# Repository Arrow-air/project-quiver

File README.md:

# Project Quiver

**An open-source, modular quadcopter platform for developers and operators.**

Project Quiver is a 25 kg MTOW drone with 5-8 kg payload capacity, three hot-swappable attachment interfaces, and a distributed electronics architecture. Built for reliability, field serviceability, and customization.

Developed by [Arrow Air](https://arrowair.com) and released under the CERN Open Hardware Licence.

## Key Features

- **Modular payload system** — Three quick-release interfaces (bottom, left, right) for mission equipment
- **Dual GNSS with RTK** — Centimeter-level positioning with backup redundancy
- **Distributed PCB architecture** — Four custom boards that can be individually serviced
- **25-31 min hover endurance** — Tattu 14S 30Ah smart battery with Hobbywing X6 Plus propulsion
- **ArduPilot firmware** — Standard QGroundControl/Mission Planner compatibility
- **Weatherproof design** — Sealed cockpit with rain canopies and drip-proof geometry

## Documentation

📖 **[Full Documentation](https://arrowair.com/quiver/)** — Platform overview, capabilities, and roadmap

The `docs/` folder is hosted on the [Arrow website](https://arrowair.com/quiver/).

| Resource | Description |
|----------|-------------|
| [Assembly Guides](https://arrowair.com/quiver/category/manufacturing/) | Step-by-step build instructions |
| [Engineering Reports](https://arrowair.com/quiver/category/reference--engineering-reports/) | Technical details for each prototype |
| [Meeting Notes](https://github.com/Arrow-air/project-quiver/wiki) | Engineering call notes |

## Repository Structure

```
project-quiver/
├── docs/                    # Documentation (hosted at arrowair.com/quiver)
├── src/
│   ├── quiver/              # CAD assembly — build123d Python package
│   ├── pcb/                 # KiCad PCB designs (4 custom boards)
│   ├── printing/            # 3D print profiles and settings
│   └── manufacturing/       # DXFs and cut sheets for CNC/laser
├── flight-test/             # Historical flight test logs
└── task-grant-bounty/       # Bounty and grant task specifications
```

### CAD Assembly

The CAD source is a [build123d](https://github.com/gumyr/build123d) Python package that composes STEP files into the full drone assembly. This enables programmatic CAD generation and version-controlled mechanical design. See [`src/quiver/`](src/quiver/) for details.

For online viewing, an interactive Fusion link of the complete Quiver assembly is available [here](https://a360.co/4kQC2ny).

For viewing online, 
## Getting Started

**Want to build one?** Start with the [Assembly Guides](https://arrowair.com/quiver/category/manufacturing/).

**Want to develop attachments?** Check out:
- [Possible Attachment List](task-grant-bounty/equipment/attachment/0001-possible_attachment_list/information-note.md)
- [Priority Attachment Requirements](task-grant-bounty/equipment/attachment/0002-detailed_attachment_requirement_for_bounty/information-note.md)

**Want a dev-kit?** Dev-kit drones are available for loan to developers with promising projects. Join the [Arrow Discord](https://discord.gg/arrow) to learn more.

## Contributing

We welcome contributions across:
- **Attachments** — Design new payloads for the modular interfaces
- **Electronics** — PCB improvements and new sensor integrations  
- **Mechanical** — Structural design and manufacturing optimization
- **Software** — ArduPilot configs, companion computer features, tooling
- **Documentation** — Guides, tutorials, and translations

See [CONTRIBUTING.md](CONTRIBUTING.md) for guidelines.

## Community

- **Discord** — [discord.gg/arrow](https://discord.gg/arrow)
- **DAO Forum** — [dao.arrowair.com](https://dao.arrowair.com)
- **Flight Tracking** — [project-flight-tracking.vercel.app](https://project-flight-tracking.vercel.app/)

## License

[CERN Open Hardware Licence Version 2 - Strongly Reciprocal (CERN-OHL-S)](LICENSE)

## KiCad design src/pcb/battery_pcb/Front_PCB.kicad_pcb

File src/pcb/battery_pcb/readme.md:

PCB files are up to date as of 01/05/26 (Front PCB V1.3, the board on the Dev-Kit aircraft). V1.2 gerbers remain in `production/` for reference.

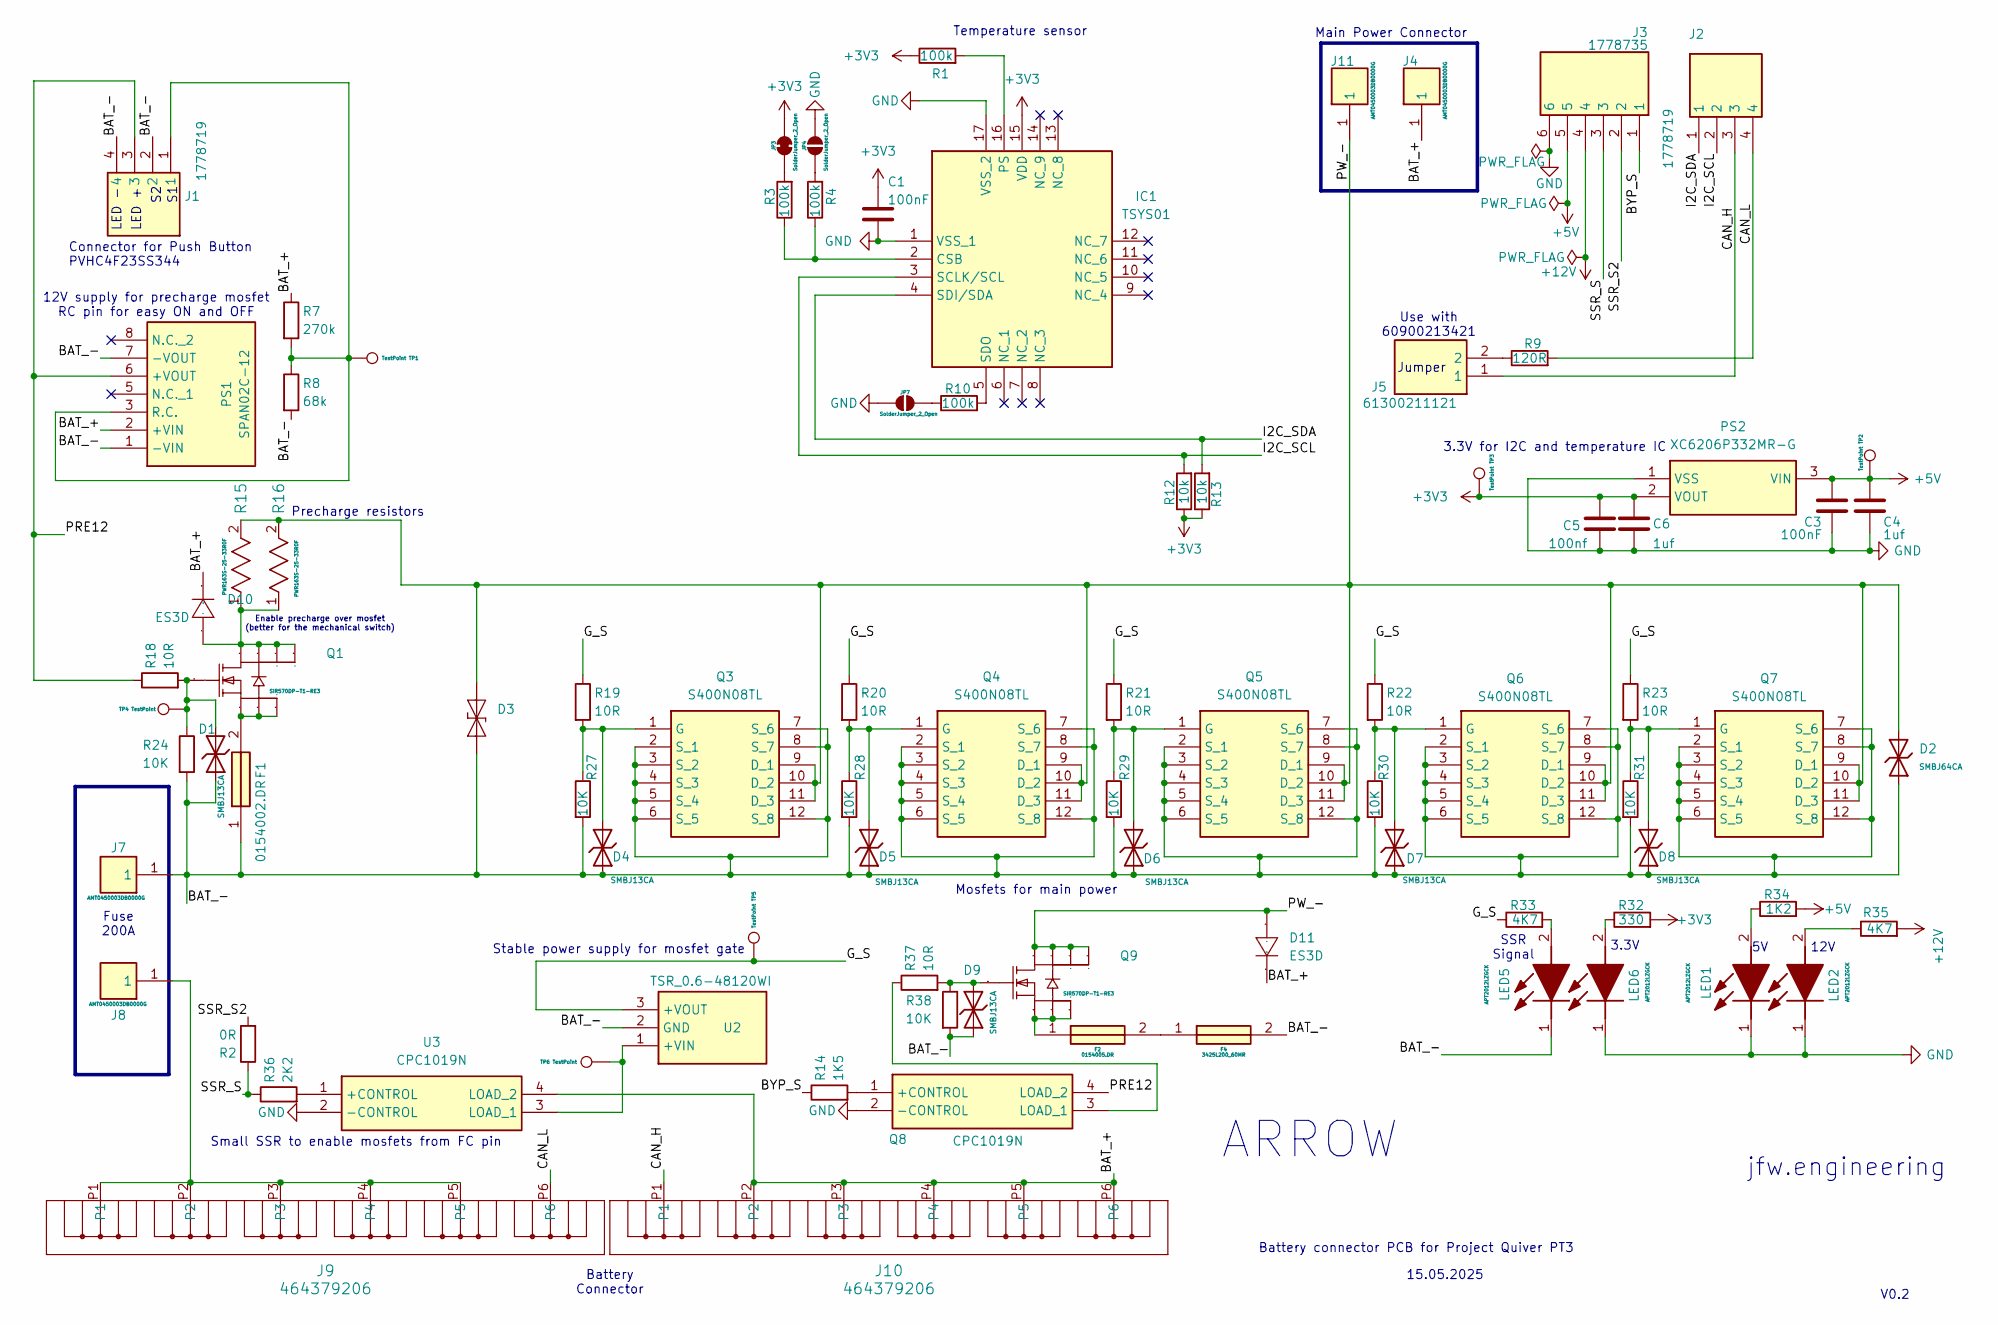
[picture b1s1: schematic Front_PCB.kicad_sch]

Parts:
C1, C3: 100nF; C_0805_2012Metric_Pad1.18x1.45mm_HandSolder
C4, C6: 1uf; C_0805_2012Metric_Pad1.18x1.45mm_HandSolder
C5: 100nf; C_0805_2012Metric_Pad1.18x1.45mm_HandSolder
D1, D4, D5, D6, D7, D8, D9: SMBJ13CA; D_SMB; Part SMBJ13CA; LCSC C19077568
D2: SMBJ64CA; D_SMB; Breakdown Voltage 78.6V; Part SMBJ64CA; LCSC C41376099
D3: SMC_L6.9-W5.9-LS7.9-BI; Manufacturer Part SMCJ75CA/TR13; LCSC Part Name SMCJ75CA/TR13
D10, D11: ES3D; D_SMC(DO-214AB); Manufacturer Part ES3D; LCSC Part Name ES3D
F1: 0154002.DR; 0154002DR; Mouser Part Number 576-0154002.DR
F2: 0154005.DR; 0154005DR; Mouser Part Number 576-0154005.DR
F4: 3425L200_60MR; FUSC8664X180N; Mouser Part Number 576-3425L200/60MR
IC1: TSYS01; QFN65P400X400X90-17N; Mouser Part Number 824-TSYS01
J1, J2: 1778719; Mouser Part Number 651-1778719
J3: 1778735; Mouser Part Number 651-1778735
J4, J7, J8, J11: AMT0450003DB0000G; Mouser Part Number 523-AMT0450003DB000G
J5: 61300211121; HDRV2W110P0X254_1X2_508X254X854P; Mouser Part Number 710-61300211121
J9, J10: 464379206; CONN_SD-46437-9000_06_MOL
JP3: SolderJumper_2_Open; SolderJumper-2_P1.3mm_Bridged2Bar_RoundedPad1.0x1.5mm
JP4, JP7: SolderJumper_2_Open; SolderJumper-2_P1.3mm_Open_RoundedPad1.0x1.5mm
LED1, LED2, LED5, LED6: APT2012LZGCK; LEDC2012X85N; Mouser Part Number 604-APT2012LZGCK
PS1: SPAN02C-12; SPAN02C12; Mouser Part Number 709-SPAN02C-12
PS2: XC6206P332MR-G; SOT95P280X130-3N; Mouser Part Number 865-XC6206P332MR-G
Q1, Q9: SIR570DP-T1-RE3; POWERPAK-SO-8_L5.9-W4.9-P1.27-LS6.2-BL; Mouser Part Number 781-SIR804DP-T1-GE3
Q3, Q4, Q5, Q6, Q7: S400N08TL; IAUT150N10S5N035ATMA1; Mouser Part Number 726-IPT017N12NM6ATMA
Q8: CPC1019N; SOP254P610X218-4N; Mouser Part Number 849-CPC1019N
R1, R3, R4, R10: 100k; R_0805_2012Metric_Pad1.20x1.40mm_HandSolder
R2: 0R; R_0805_2012Metric_Pad1.20x1.40mm_HandSolder
R7: 270k; R_0805_2012Metric_Pad1.20x1.40mm_HandSolder
R8: 68k; R_0805_2012Metric_Pad1.20x1.40mm_HandSolder
R9: 120R; R_0805_2012Metric_Pad1.20x1.40mm_HandSolder
R12, R13: 10k; R_0805_2012Metric_Pad1.20x1.40mm_HandSolder
R14: 1K5; R_0805_2012Metric_Pad1.20x1.40mm_HandSolder
R15, R16: PWR163S-25-33R0F; RES_PWR163_BRN; PARTREV 0716
R18, R19, R20, R21, R22, R23, R37: 10R; R_0805_2012Metric_Pad1.20x1.40mm_HandSolder
R24, R27, R28, R29, R30, R31, R38: 10K; R_0805_2012Metric_Pad1.20x1.40mm_HandSolder
R32: 330; R_0805_2012Metric_Pad1.20x1.40mm_HandSolder
R33, R35: 4K7; R_0805_2012Metric_Pad1.20x1.40mm_HandSolder
R34: 1K2; R_0805_2012Metric_Pad1.20x1.40mm_HandSolder
R36: 2K2; R_0805_2012Metric_Pad1.20x1.40mm_HandSolder
TP1, TP2, TP3, TP4, TP5, TP6: TestPoint; TestPoint_Pad_D1.5mm
U2: TSR_0.6-48120WI; TSR0648120WI; Mouser Part Number 495-TSR0.6-48120WI
U3: CPC1019N; SOP254P610X218-4N; Mouser Part Number 849-CPC1019N

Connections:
+3V3: C1.1, C5.1, C6.1, IC1.15 (VDD), JP3.2 (B), PS2.2 (VOUT), R1.1, R12.1, R13.1, R32.2, TP3.1
+5V: C3.1, C4.1, J3.5, PS2.3 (VIN), R34.2, TP2.1
+12V: J3.4, R35.2
/BAT_+: D10.1, D11.1, J4.1, J10.P2, J10.P3, J10.P4, J10.P5, J10.P6, PS1.2 (+VIN), R7.1, U3.4 (LOAD_2)
/BAT_-: D1.1, D2.1, D3.1 (K), D4.1, D5.1, D6.1, D7.1, D8.1, D9.1, F1.1, F4.2, J1.2, J1.4, J7.1, LED5.1 (K), PS1.1 (-VIN), PS1.7 (-VOUT), Q3.2 (S_1), Q3.3 (S_2), Q3.4 (S_3), Q3.5 (S_4), Q3.6 (S_5), Q3.7 (S_6), Q3.8 (S_7), Q3.12 (S_8), Q4.2 (S_1), Q4.3 (S_2), Q4.4 (S_3), Q4.5 (S_4), Q4.6 (S_5), Q4.7 (S_6), Q4.8 (S_7), Q4.12 (S_8), Q5.2 (S_1), Q5.3 (S_2), Q5.4 (S_3), Q5.5 (S_4), Q5.6 (S_5), Q5.7 (S_6), Q5.8 (S_7), Q5.12 (S_8), Q6.2 (S_1), Q6.3 (S_2), Q6.4 (S_3), Q6.5 (S_4), Q6.6 (S_5), Q6.7 (S_6), Q6.8 (S_7), Q6.12 (S_8), Q7.2 (S_1), Q7.3 (S_2), Q7.4 (S_3), Q7.5 (S_4), Q7.6 (S_5), Q7.7 (S_6), Q7.8 (S_7), Q7.12 (S_8), R8.2, R24.2, R27.2, R28.2, R29.2, R30.2, R31.2, R38.2, U2.2 (GND)
/BYP_S: J3.1, R14.1
/CAN_H: J2.3, J5.1, J10.P1
/CAN_L: J2.4, J9.P6, R9.2
/G_S: R19.1, R20.1, R21.1, R22.1, R23.1, R33.1, TP5.1, U2.3 (+VOUT)
/I2C_SCL: IC1.3 (SCLK/SCL), J2.2, R12.2
/I2C_SDA: IC1.4 (SDI/SDA), J2.1, R13.2
/PRE12: J1.3, PS1.6 (+VOUT), Q8.4 (LOAD_2), R18.1
/PW_-: D2.2, D3.2 (A), D11.2, J11.1, Q3.9 (D_1), Q3.10 (D_2), Q3.11 (D_3), Q4.9 (D_1), Q4.10 (D_2), Q4.11 (D_3), Q5.9 (D_1), Q5.10 (D_2), Q5.11 (D_3), Q6.9 (D_1), Q6.10 (D_2), Q6.11 (D_3), Q7.9 (D_1), Q7.10 (D_2), Q7.11 (D_3), Q9.5 (D), Q9.6 (D), Q9.7 (D), Q9.8 (D), R15.2, R16.2
/SSR_S: J3.3, R2.1, R36.1
/SSR_S2: J3.2, R2.2
GND: C1.2, C3.2, C4.2, C5.2, C6.2, IC1.1 (VSS_1), IC1.17 (VSS_2), J3.6, JP4.2 (B), JP7.1 (A), LED1.1 (K), LED2.1 (K), LED6.1 (K), PS2.1 (VSS), Q8.2 (-CONTROL), U3.2 (-CONTROL)
unnamed: D10.2, Q1.5 (D), Q1.6 (D), Q1.7 (D), Q1.8 (D), R15.1, R16.1
unnamed: F1.2, Q1.1 (S), Q1.2 (S), Q1.3 (S)
unnamed: F2.1, Q9.1 (S), Q9.2 (S), Q9.3 (S)
unnamed: F2.2, F4.1
unnamed: IC1.2 (CSB), R3.1, R4.1
unnamed: IC1.16 (PS), R1.2
unnamed: IC1.5 (SDO), R10.2
unnamed: J5.2, R9.1
unnamed: J8.1, J9.P1, J9.P2, J9.P3, J9.P4, J9.P5
unnamed: JP3.1 (A), R3.2
unnamed: JP4.1 (A), R4.2
unnamed: JP7.2 (B), R10.1
unnamed: LED1.2 (A), R34.1
unnamed: LED2.2 (A), R35.1
unnamed: LED5.2 (A), R33.2
unnamed: LED6.2 (A), R32.1
unnamed: J1.1, PS1.3 (R.C.), R7.2, R8.1, TP1.1
unnamed: D1.2, Q1.4 (G), R18.2, R24.1, TP4.1
unnamed: D4.2, Q3.1 (G), R19.2, R27.1
unnamed: D5.2, Q4.1 (G), R20.2, R28.1
unnamed: D6.2, Q5.1 (G), R21.2, R29.1
unnamed: D7.2, Q6.1 (G), R22.2, R30.1
unnamed: D8.2, Q7.1 (G), R23.2, R31.1
unnamed: Q8.1 (+CONTROL), R14.2
unnamed: Q8.3 (LOAD_1), R37.1
unnamed: D9.2, Q9.4 (G), R37.2, R38.1
unnamed: TP6.1, U2.1 (+VIN), U3.3 (LOAD_1)
unnamed: R36.2, U3.1 (+CONTROL)

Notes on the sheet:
15.05.2025
Connector for Push Button PVHC4F23SS344
Battery connector PCB for Project Quiver PT3
SSR Signal
3.3V
12V supply for precharge mosfet RC pin for easy ON and OFF
Use with 60900213421
12V
Battery Connector
ARROW
Temperature sensor
Small SSR to enable mosfets from FC pin
3.3V for I2C and temperature IC
Jumper
Mosfets for main power
LED -
Stable power supply for mosfet gate
V0.2
jfw.engineering
Enable precharge over mosfet (better for the mechanical switch)
LED +
Main Power Connector
Fuse 200A
Precharge resistors

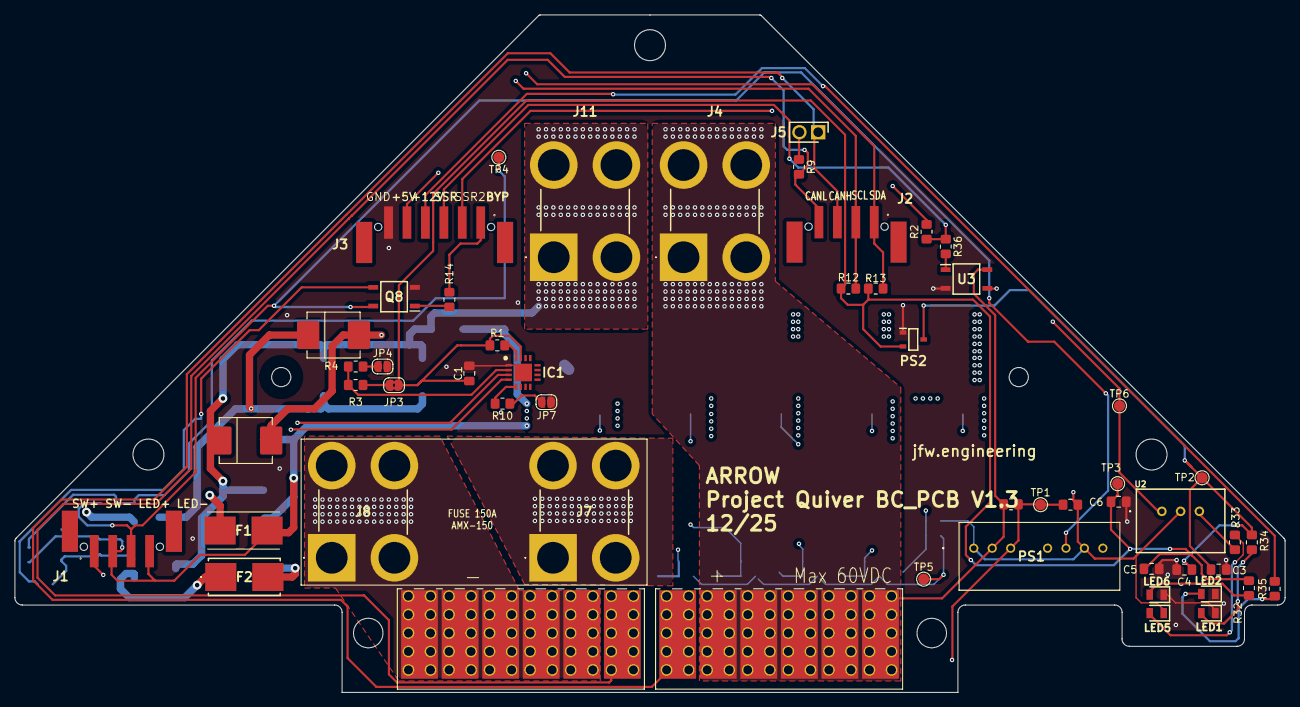
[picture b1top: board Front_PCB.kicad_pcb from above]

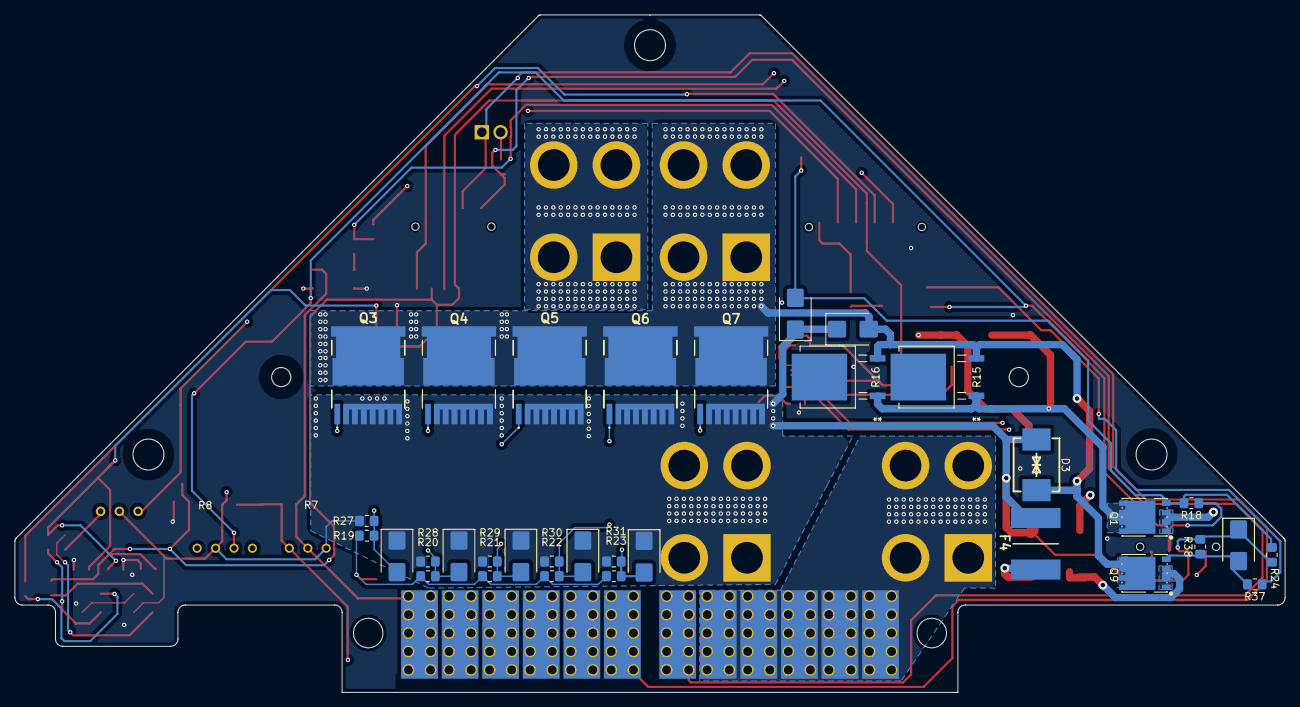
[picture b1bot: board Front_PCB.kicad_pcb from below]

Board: 4 copper layers, 172.2 x 91.8 mm, 87 parts (33 on the bottom side), 44 nets.

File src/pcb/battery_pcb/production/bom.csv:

Designator,Footprint,Quantity,Value,LCSC Part #
"C1, C3, C5",0805,3,100nF,
"C4, C6",0805,2,1uf,
"D1, D4, D5, D6, D7, D8, D9",D_SMB,7,SMBJ13CA,C19077568
"D10, D11",D_SMC(DO-214AB),2,ES3D,
D2,D_SMB,1,SMBJ64CA,C41376099
D3,SMC_L6.9-W5.9-LS7.9-BI,1,~,
F1,0154002DR,1,0154002.DR,
F2,0154005DR,1,0154005.DR,
F4,FUSC8664X180N,1,3425L200_60MR,
IC1,QFN65P400X400X90-17N,1,TSYS01,
"J1, J2",1778719,2,1778719,
"J10, J9",CONN_SD-46437-9000_06_MOL,2,464379206,
"J11, J4, J7, J8",AMT0450003DB0000G,4,AMT0450003DB0000G,
J3,1778735,1,1778735,
J5,HDRV2W110P0X254_1X2_508X254X854P,1,61300211121,
"LED1, LED2, LED5, LED6",LEDC2012X85N,4,APT2012LZGCK,
PS1,SPAN02C12,1,SPAN02C-12,
PS2,SOT95P280X130-3N,1,XC6206P332MR-G,
"Q1, Q9",POWERPAK-SO-8_L5.9-W4.9-P1.27-LS6.2-BL,2,SIR570DP-T1-RE3,
"Q3, Q4, Q5, Q6, Q7",IAUT150N10S5N035ATMA1,5,S400N08TL,
"Q8, U3",SOP254P610X218-4N,2,CPC1019N,
"R1, R10, R3, R4",0805,4,100k,
"R12, R13, R24, R27, R28, R29, R30, R31, R38",0805,9,10k,
R14,0805,1,1K5,
"R15, R16",RES_PWR163_BRN,2,PWR163S-25-33R0F,
"R18, R19, R20, R21, R22, R23, R37",0805,7,10R,
R2,0805,1,0R,
R32,0805,1,330,
"R33, R35",0805,2,4K7,
R34,0805,1,1K2,
R36,0805,1,2K2,
R7,0805,1,270k,
R8,0805,1,68k,
R9,0805,1,120R,
"TP1, TP2, TP3, TP4, TP5, TP6",TestPoint_Pad_D1.5mm,6,TestPoint,
U2,TSR0648120WI,1,TSR_0.6-48120WI,

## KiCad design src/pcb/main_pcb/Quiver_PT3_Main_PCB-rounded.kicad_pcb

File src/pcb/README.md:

# PCB Designs

KiCad projects for the Quiver's distributed PCB architecture.

## Board projects

| Directory | BOM | KiCad project | Description |
|---|---|---|---|
| `battery_pcb/` | 3320 | `Front_PCB` (V1.3) | Battery PCB — power switching and protection |
| `main_pcb/` | 3310 | `Quiver_PT3_Main_PCB-rounded` (V1.2) | Main PCB — power and data distribution hub. V1.2 is the board on the Dev-Kit aircraft. |
| `fc_pcb/` | 3330 | `Quiver_PT3_FC_PCB` | Flight Controller PCB — Pix32 V6 adapter board |
| `attach_pcb/` | 3331 | `QuiverAttachPCB` (V1.4) | Attachment Interface PCB (x3) |

Production gerbers live in each project's `production/` folder. Design
history, update notes, and superseded board revisions remain with the
bounty tasks under
[`task-grant-bounty/pt3/electronics/`](../../task-grant-bounty/pt3/electronics/).

## STEP export workflow

Each KiCad project can export a 3D STEP model of the assembled board
(`kicad-cli pcb export step --subst-models <board>.kicad_pcb`). The CAD
assembly uses these models:

```
pcb/<board>/  ──(KiCad 3D export)──►  ../quiver/equipment/pcb/steps/vendor/{BOM}_{name}.step
```

For example, `main_pcb` is `3310_main_pcb.step` and `battery_pcb` is
`3320_bc_pcb.step` in `../quiver/equipment/pcb/steps/vendor/`.

The CAD models also carry parts whose 3D models are not in these KiCad
libraries: `3320_bc_pcb.step` includes the 3324 heatsink with its screws
and a few connector and component bodies. A plain KiCad export is missing
them, so before replacing a CAD model, check that its board body matches
the KiCad source and carry those parts over. The board bodies in 3310 and
3320 match the V1.2 and V1.3 sources exactly.

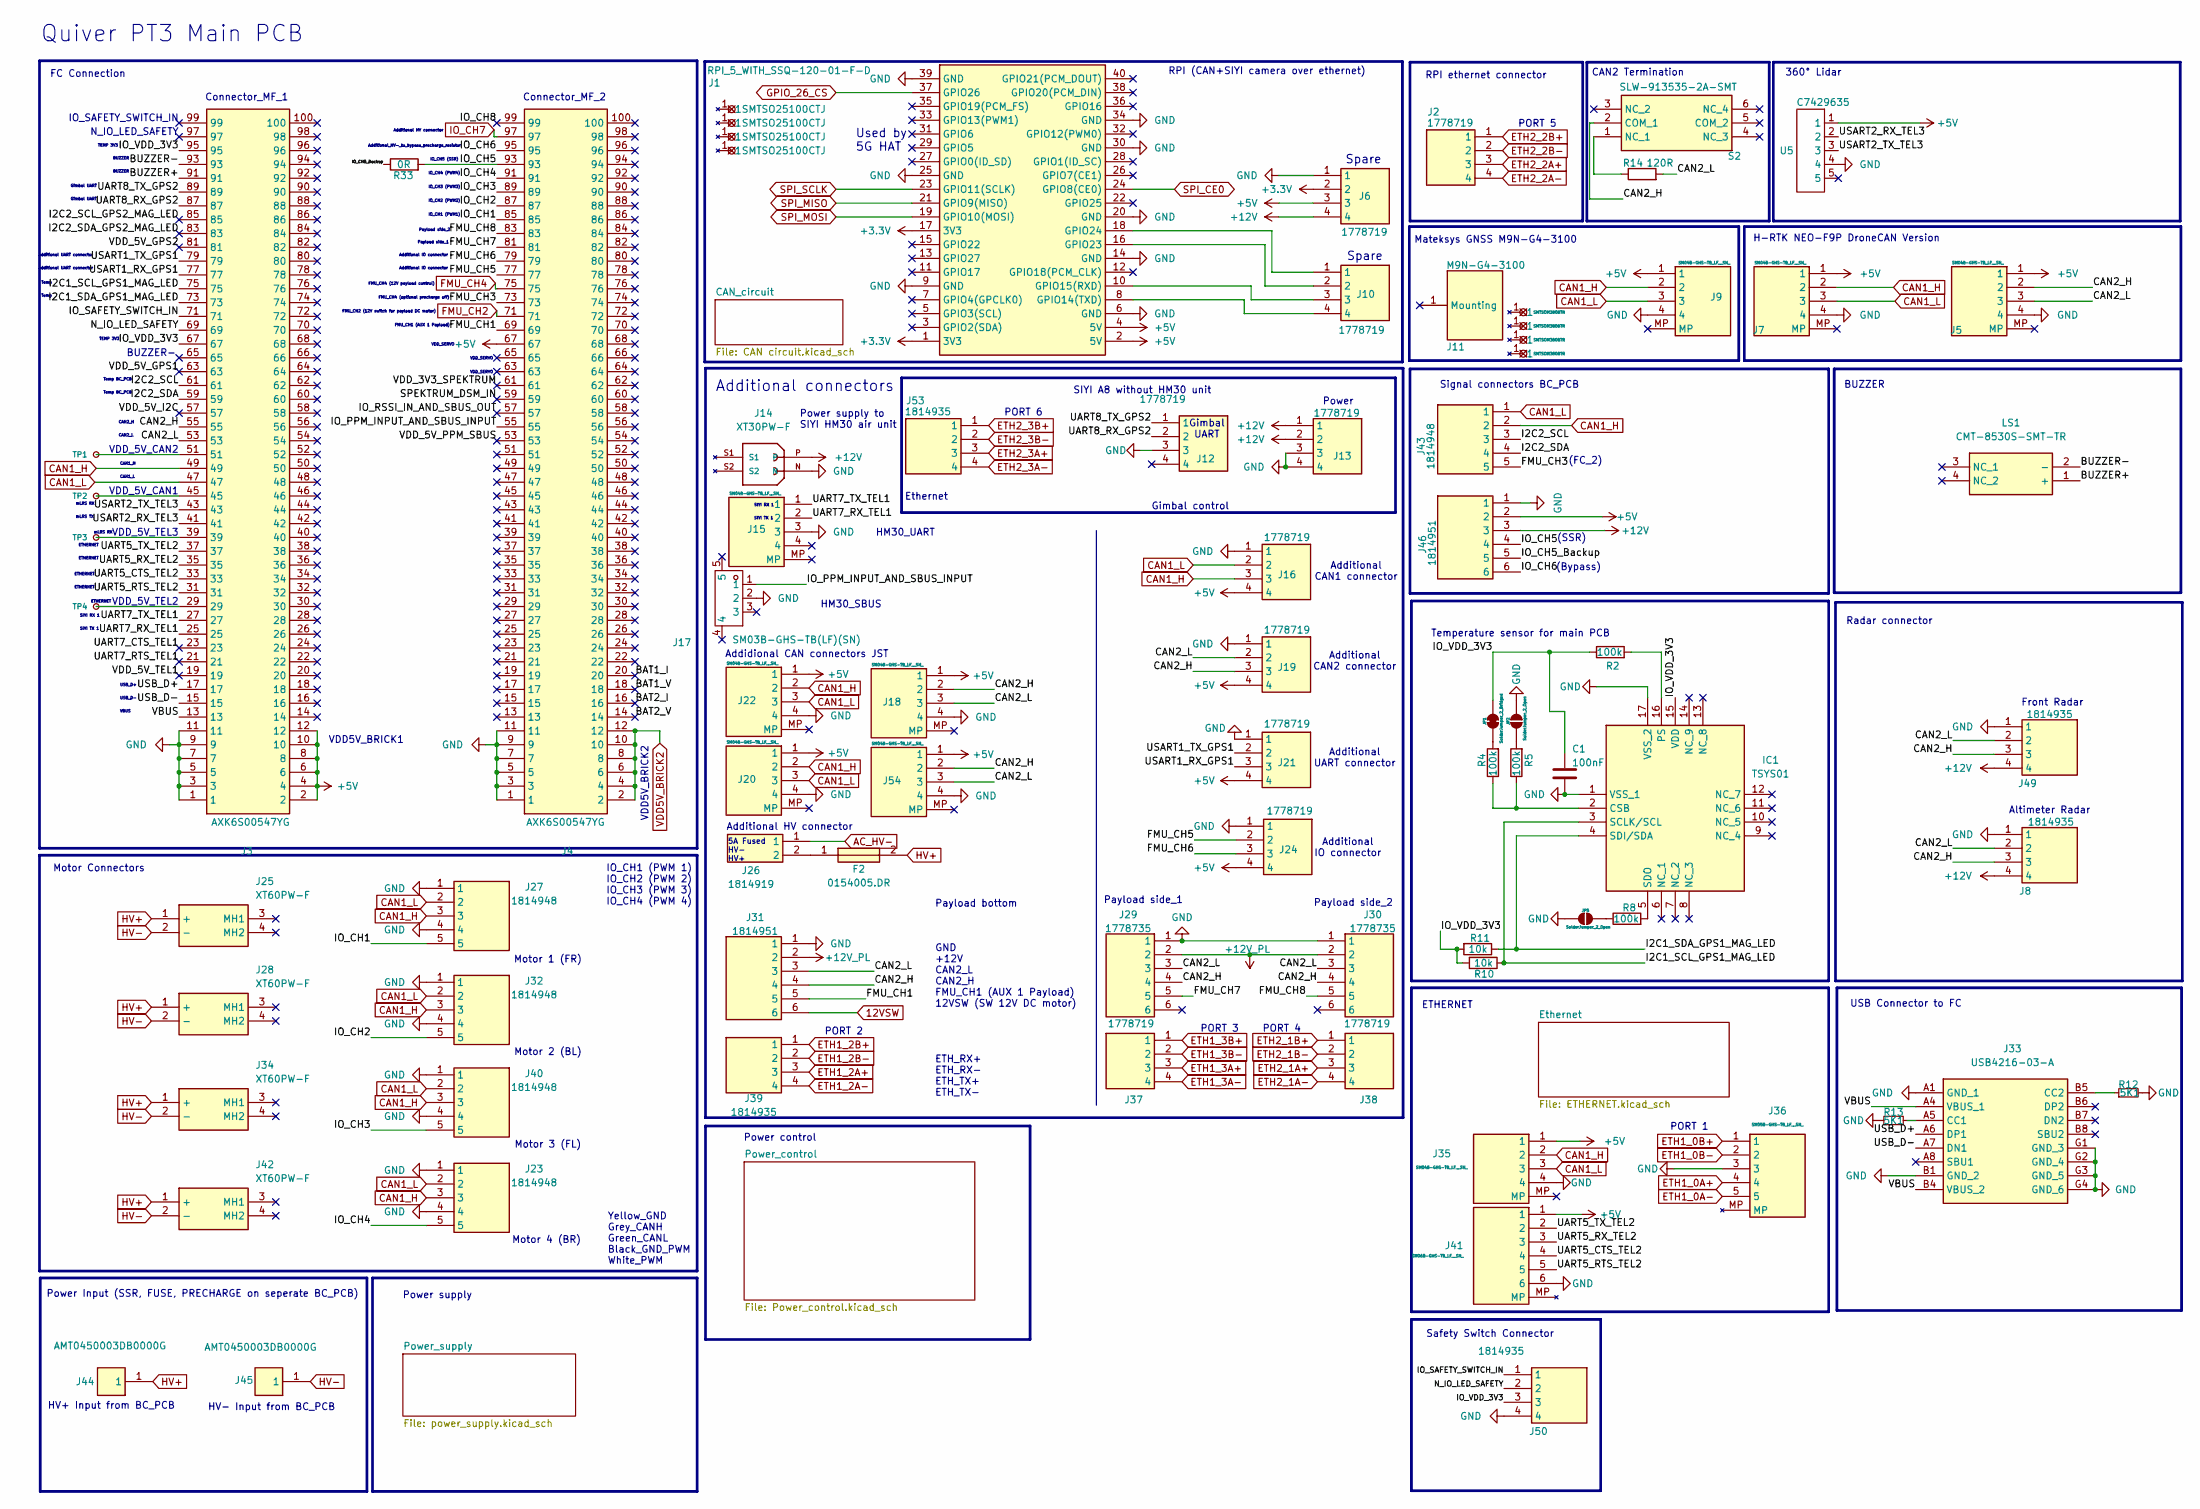
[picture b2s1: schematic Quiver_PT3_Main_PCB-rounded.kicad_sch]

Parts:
C1: 100nF; C_0805_2012Metric_Pad1.18x1.45mm_HandSolder; MPN CC0805KRX7R9BB104
F2: 0154005.DR; 0154005DR; Mouser Part Number 576-0154005.DR
IC1: TSYS01; QFN65P400X400X90-17N; Mouser Part Number 824-TSYS01
J1: RPI_5_WITH_SSQ-120-01-F-D; SSM-120-XXX-DV; Mouser Part Number 200-SSQ12001FD
J2, J6, J10, J12, J13, J16, J19, J21, J24, J37, J38: 1778719; Mouser Part Number 651-1778719
J3, J4: AXK6S00547YG; MANUFACTURER_PART_NUMBER AXK5S00347YG; Mouser Part Number 769-AXK6S00547YG
J5, J7, J9, J15, J18, J20, J22, J35, J54: SM04B-GHS-TB_LF__SN_; SM04B-GHS-TB; Mouser Part Number N/A
J8, J39, J49, J50, J53: 1814935; Mouser Part Number 651-1814935
J11: M9N-G4-3100; Manufacturer_Part_Number SSQ-104-01-L-D
J14: XT30PW-F; XT30PW-F_AMASS_XT30PW-F; PARTREV 1.2
J17: SM03B-GHS-TB(LF)(SN); CONN-TH_SM03B-GHS-TB-LF-SN; Mouser Part Number 651-1814922
J23, J27, J32, J40, J43: 1814948; Mouser Part Number 651-1814948
J25, J28, J34, J42: XT60PW-F; XT60PWF; Manufacturer_Part_Number XT60PW-F
J26: 1814919; Mouser Part Number 651-1814919
J29, J30: 1778735; Mouser Part Number 651-1778735
J31, J46: 1814951; Mouser Part Number 651-1814951
J33: USB4216-03-A; USB421603A; Mouser Part Number 640-USB4216-03-A
J36: SM05B-GHS-TB_LF__SN_; SM05B-GHS-TB; Mouser Part Number N/A
J41: SM06B-GHS-TB_LF__SN_; SM06B-GHS-TB; Mouser Part Number N/A
J44, J45: AMT0450003DB0000G; Mouser Part Number 523-AMT0450003DB000G
JP1: SolderJumper_2_Bridged; SolderJumper-2_P1.3mm_Bridged2Bar_RoundedPad1.0x1.5mm
JP2, JP5: SolderJumper_2_Open; SolderJumper-2_P1.3mm_Open_RoundedPad1.0x1.5mm
LS1: CMT-8530S-SMT-TR; CMT8530SSMTTR; Mouser Part Number 490-CMT-8530S-SMT-TR
R2, R4, R5: 100k; R_0805_2012Metric_Pad1.20x1.40mm_HandSolder
R8: 100k; R_0805_2012Metric_Pad1.20x1.40mm_HandSolder; MPN RC0805FR-0710KL
R10, R11: 10k; R_0805_2012Metric_Pad1.20x1.40mm_HandSolder; MPN RC0805FR-0710KL
R12, R13: 5K1; R_0805_2012Metric_Pad1.20x1.40mm_HandSolder
R14: 120R; R_0805_2012Metric_Pad1.20x1.40mm_HandSolder; MPN RC0805FR-07120RL
R33: 0R; R_0805_2012Metric_Pad1.20x1.40mm_HandSolder
S2: SLW-913535-2A-SMT; SLW9135352ASMT; MPN SLW-913535-2A-SMT; Mouser Part Number 179-SLW-913535-2ASMT
TP1, TP2, TP3, TP4: TestPoint_Small; TestPoint_Pad_1.0x1.0mm
U3, U6, U7, U8: SMTSOM380BTR; SMD_BD6.0-D4.2; Manufacturer Part SMTSOM380BTR; LCSC Part Name YIYUAN(怡远) 电路板表贴圆螺母柱 PCB贴片连接器 M3x5.56xL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
U5: C7429635; CONN-TH_5P-P2.50_ZX-XH2.54-5PZZ; Mouser Part Number 651-1814935
U9, U10, U11, U12: SMTSO25100CTJ; SMD_BD5.6-L5.6-W5.6-D4.1; Manufacturer Part SMTSO25100CTJ; LCSC Part Name 雄和远景，电路板表贴圆螺母柱，M2.5X10，铜镀锡,1个

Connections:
12VSW: J31.6; also elsewhere on the board
+3.3V: J1.1 (3V3), J1.17 (3V3), J6.2; also elsewhere on the board
+5V: J1.2 (5V), J1.4 (5V), J3.2, J3.4, J3.6, J3.8, J3.10, J3.12, J4.67, J5.1, J6.3, J7.1, J9.1, J16.4, J18.1, J19.4, J20.1, J21.4, J22.1, J24.4, J35.1, J41.1, J46.2, J54.1, U5.1; also elsewhere on the board
+12V: J6.4, J8.4, J13.1, J13.2, J14.P, J46.3, J49.4; also elsewhere on the board
+12V_PL: J29.2, J30.2, J31.2; also elsewhere on the board
/ I2C2_SDA_GPS2_MAG_LED: J3.83
/BAT1_I: J4.20
/BAT1_V: J4.18
/BAT2_I: J4.16
/BAT2_V: J4.14
/BUZZER+: J3.91, LS1.1 (+)
/BUZZER-: J3.93, LS1.2 (-)
/CAN2_H: J3.55, J5.2, J8.3, J18.2, J19.3, J29.4, J30.4, J31.4, J49.3, J54.2, S2.2 (COM_1)
/CAN2_L: J3.53, J5.3, J8.2, J18.3, J19.2, J29.3, J30.3, J31.3, J49.2, J54.3, R14.2
/FMU_CH1: J4.69, J31.5
/FMU_CH3: J4.73, J43.5
/FMU_CH5: J4.77, J24.2
/FMU_CH6: J4.79, J24.3
/FMU_CH7: J4.81, J29.5
/FMU_CH8: J4.83, J30.5
/I2C1_SCL_GPS1_MAG_LED: IC1.3 (SCLK/SCL), J3.75, R10.1
/I2C1_SDA_GPS1_MAG_LED: IC1.4 (SDI/SDA), J3.73, R11.1
/I2C2_SCL: J3.61, J43.3
/I2C2_SCL_GPS2_MAG_LED: J3.85
/I2C2_SDA: J3.59, J43.4
/IO_CH1: J4.85, J27.5
/IO_CH2: J4.87, J32.5
/IO_CH3: J4.89, J40.5
/IO_CH4: J4.91, J23.5
/IO_CH5: J4.93, J46.4, R33.2
/IO_CH5_Backup: J46.5, R33.1
/IO_CH6: J4.95, J46.6
/IO_CH8: J4.99
/IO_PPM_INPUT_AND_SBUS_INPUT: J4.55, J17.1
/IO_RSSI_IN_AND_SBUS_OUT: J4.57
/IO_SAFETY_SWITCH_IN: J3.71, J50.1
/IO_VDD_3V3: C1.1, IC1.15 (VDD), J3.67, J3.95, J50.3, JP1.2 (B), R2.1, R10.2, R11.2
/N_IO_LED_SAFETY: J3.69, J50.2
/SPEKTRUM_DSM_IN: J4.59
/UART5_CTS_TEL2: J3.33, J41.4
/UART5_RTS_TEL2: J3.31, J41.5
/UART5_RX_TEL2: J3.35, J41.3
/UART5_TX_TEL2: J3.37, J41.2
/UART7_CTS_TEL1: J3.23
/UART7_RTS_TEL1: J3.21
/UART7_RX_TEL1: J3.25, J15.2
/UART7_TX_TEL1: J3.27, J15.1
/UART8_RX_GPS2: J3.87, J12.2
/UART8_TX_GPS2: J3.89, J12.1
/USART1_RX_GPS1: J3.77, J21.3
/USART1_TX_GPS1: J3.79, J21.2
/USART2_RX_TEL3: J3.41, U5.2
/USART2_TX_TEL3: J3.43, U5.3
/USB_D+: J3.17, J33.A6 (DP1)
/USB_D-: J3.15, J33.A7 (DN1)
/VBUS: J3.13, J33.A4 (VBUS_1), J33.B4 (VBUS_2)
/VDD_3V3_SPEKTRUM: J4.61
/VDD_5V_GPS1: J3.63
/VDD_5V_GPS2: J3.81
/VDD_5V_I2C: J3.57
/VDD_5V_PPM_SBUS: J4.53
/VDD_5V_TEL1: J3.19
AC_HV-: J26.1; also elsewhere on the board
CAN1_H: J3.49, J7.2, J9.2, J16.3, J20.2, J22.2, J23.3, J27.3, J32.3, J35.2, J40.3, J43.2; also elsewhere on the board
CAN1_L: J3.47, J7.3, J9.3, J16.2, J20.3, J22.3, J23.2, J27.2, J32.2, J35.3, J40.2, J43.1; also elsewhere on the board
ETH1_0A+: J36.4; also elsewhere on the board
ETH1_0A-: J36.5; also elsewhere on the board
ETH1_0B+: J36.1; also elsewhere on the board
ETH1_0B-: J36.2; also elsewhere on the board
ETH1_2A+: J39.3; also elsewhere on the board
ETH1_2A-: J39.4; also elsewhere on the board
ETH1_2B+: J39.1; also elsewhere on the board
ETH1_2B-: J39.2; also elsewhere on the board
ETH1_3A+: J37.3; also elsewhere on the board
ETH1_3A-: J37.4; also elsewhere on the board
ETH1_3B+: J37.1; also elsewhere on the board
ETH1_3B-: J37.2; also elsewhere on the board
ETH2_1A+: J38.3; also elsewhere on the board
ETH2_1A-: J38.4; also elsewhere on the board
ETH2_1B+: J38.1; also elsewhere on the board
ETH2_1B-: J38.2; also elsewhere on the board
ETH2_2A+: J2.3; also elsewhere on the board
ETH2_2A-: J2.4; also elsewhere on the board
ETH2_2B+: J2.1; also elsewhere on the board
ETH2_2B-: J2.2; also elsewhere on the board
ETH2_3A+: J53.3; also elsewhere on the board
ETH2_3A-: J53.4; also elsewhere on the board
ETH2_3B+: J53.1; also elsewhere on the board
ETH2_3B-: J53.2; also elsewhere on the board
FMU_CH2: J4.71; also elsewhere on the board
FMU_CH4: J4.75; also elsewhere on the board
GND: C1.2, IC1.1 (VSS_1), IC1.17 (VSS_2), J1.6 (GND), J1.9 (GND), J1.14 (GND), J1.20 (GND), J1.25 (GND), J1.30 (GND), J1.34 (GND), J1.39 (GND), J3.1, J3.3, J3.5, J3.7, J3.9, J3.11, J4.1, J4.3, J4.5, J4.7, J4.9, J4.11, J5.4, J6.1, J7.4, J8.1, J9.4, J12.3, J13.3, J13.4, J14.N, J15.3, J16.1, J17.2, J18.4, J19.1, J20.4, J21.1, J22.4, J23.1, J23.4, J24.1, J27.1, J27.4, J29.1, J30.1, J31.1, J32.1, J32.4, J33.A1 (GND_1), J33.B1 (GND_2), J33.G1 (GND_3), J33.G2 (GND_4), J33.G3 (GND_5), J33.G4 (GND_6), J35.4, J36.3, J40.1, J40.4, J41.6, J46.1, J49.1, J50.4, J54.4, JP2.2 (B), JP5.1 (A), R12.2, R13.1, U5.4; also elsewhere on the board
GPIO_26_CS: J1.37 (GPIO26); also elsewhere on the board
HV+: F2.2, J25.1 (+), J28.1 (+), J34.1 (+), J42.1 (+), J44.1; also elsewhere on the board
HV-: J25.2 (-), J28.2 (-), J34.2 (-), J42.2 (-), J45.1; also elsewhere on the board
IO_CH7: J4.97; also elsewhere on the board
unnamed: F2.1, J26.2
unnamed: IC1.2 (CSB), R4.1, R5.1
unnamed: IC1.16 (PS), R2.2
unnamed: IC1.5 (SDO), R8.2
unnamed: J1.8 (GPIO14(TXD)), J10.4
unnamed: J1.10 (GPIO15(RXD)), J10.3
unnamed: J1.16 (GPIO23), J10.2
unnamed: J1.18 (GPIO24), J10.1
unnamed: J3.29, TP4.1
unnamed: J3.39, TP3.1
unnamed: J3.45, TP2.1
unnamed: J3.51, TP1.1
unnamed: J33.A5 (CC1), R13.2
unnamed: J33.B5 (CC2), R12.1
unnamed: JP1.1 (A), R4.2
unnamed: JP2.1 (A), R5.2
unnamed: JP5.2 (B), R8.1
unnamed: R14.1, S2.1 (NC_1)
SPI_CE0: J1.24 (GPIO8(CE0)); also elsewhere on the board
SPI_MISO: J1.21 (GPIO9(MISO)); also elsewhere on the board
SPI_MOSI: J1.19 (GPIO10(MOSI)); also elsewhere on the board
SPI_SCLK: J1.23 (GPIO11(SCLK)); also elsewhere on the board
VDD5V_BRICK2: J4.2, J4.4, J4.6, J4.8, J4.10, J4.12; also elsewhere on the board

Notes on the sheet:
ETHERNET
Altimeter Radar
TEMP 3V3
IO_CH2 (PWM2)
Additional CAN2 connector
Additional HV connector
PORT 5
Motor Connectors
Motor 4 (BR)
FMU_CH4 (optional precharge off)
FC Connection
Motor 2 (BL)
FMU_CH4 (12V payload control)
BUZZER BUZZER
Used by 5G HAT
Temperature sensor for main PCB
Power Input (SSR, FUSE, PRECHARGE on seperate BC_PCB)
USB_D+ USB_D- VBUS
PORT 4
ETHERNET ETHERNET
FMU_CH2 (12V switch for payload DC motor)
Payload side_2
(Bypass)
IO_CH5 (SSR)
PORT 3
Connector_MF_2
N_IO_LED_SAFETY
CAN2 Termination
HM30_SBUS
VDD5V_BRICK1
FMU_CH1 (AUX 1 Payload)
USB Connector to FC
VDD5V_BRICK2
(FC_2)
Power
VDD_SERVO
RPI (CAN+SIYI camera over ethernet)
IO_CH4 (PWM4)
Gimbal UART Gimbal UART
Power supply

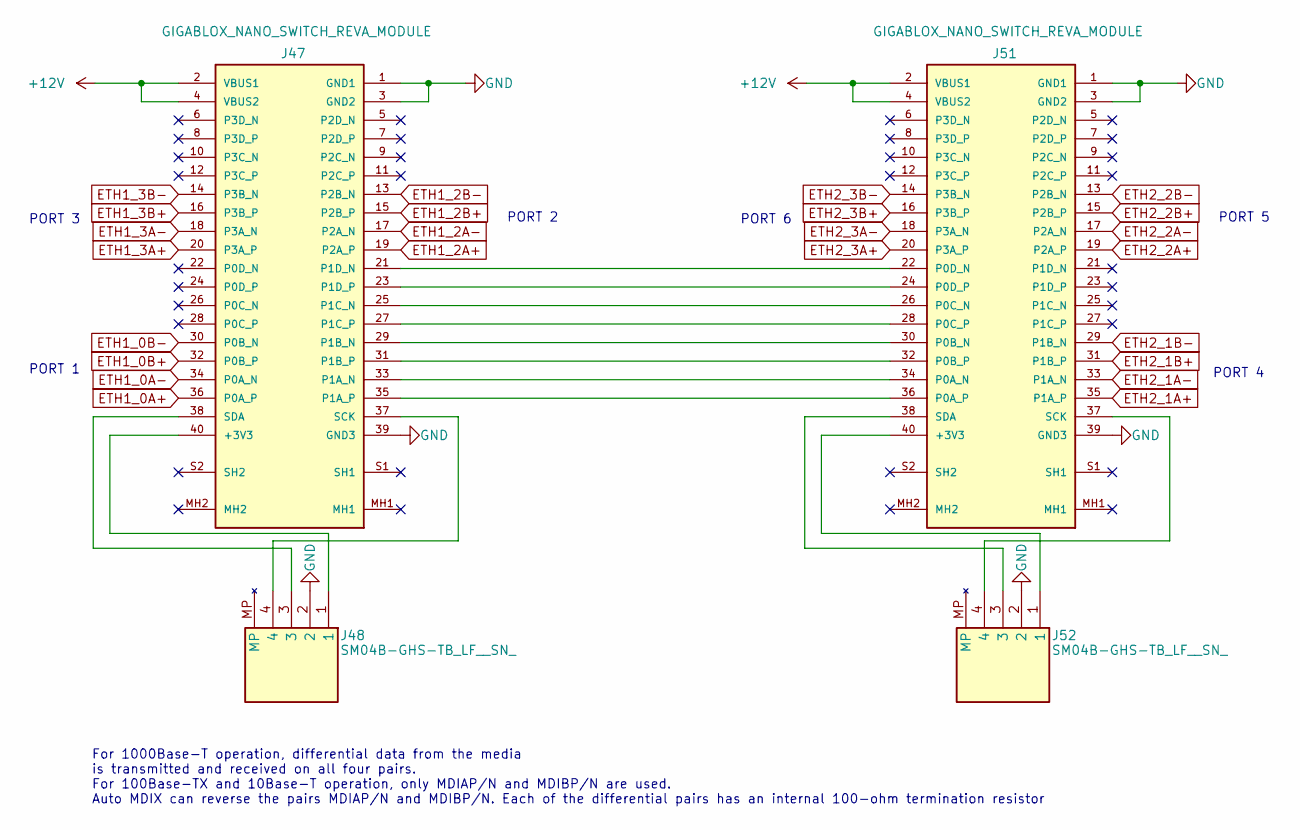
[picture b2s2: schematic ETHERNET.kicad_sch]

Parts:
J47, J51: GIGABLOX_NANO_SWITCH_REVA_MODULE; GIGABLOX_NANO_SWITCH_REVA_MODULE_LSHM-120-02.5-L-DV-A-S-K-TR; Mouser Part Number 200-LSHM1202.5LDVASK
J48, J52: SM04B-GHS-TB_LF__SN_; SM04B-GHS-TB; Mouser Part Number N/A

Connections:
+12V: J47.2 (VBUS1), J47.4 (VBUS2), J51.2 (VBUS1), J51.4 (VBUS2); also elsewhere on the board
ETH1_0A+: J47.36 (P0A_P); also elsewhere on the board
ETH1_0A-: J47.34 (P0A_N); also elsewhere on the board
ETH1_0B+: J47.32 (P0B_P); also elsewhere on the board
ETH1_0B-: J47.30 (P0B_N); also elsewhere on the board
ETH1_2A+: J47.19 (P2A_P); also elsewhere on the board
ETH1_2A-: J47.17 (P2A_N); also elsewhere on the board
ETH1_2B+: J47.15 (P2B_P); also elsewhere on the board
ETH1_2B-: J47.13 (P2B_N); also elsewhere on the board
ETH1_3A+: J47.20 (P3A_P); also elsewhere on the board
ETH1_3A-: J47.18 (P3A_N); also elsewhere on the board
ETH1_3B+: J47.16 (P3B_P); also elsewhere on the board
ETH1_3B-: J47.14 (P3B_N); also elsewhere on the board
ETH2_1A+: J51.35 (P1A_P); also elsewhere on the board
ETH2_1A-: J51.33 (P1A_N); also elsewhere on the board
ETH2_1B+: J51.31 (P1B_P); also elsewhere on the board
ETH2_1B-: J51.29 (P1B_N); also elsewhere on the board
ETH2_2A+: J51.19 (P2A_P); also elsewhere on the board
ETH2_2A-: J51.17 (P2A_N); also elsewhere on the board
ETH2_2B+: J51.15 (P2B_P); also elsewhere on the board
ETH2_2B-: J51.13 (P2B_N); also elsewhere on the board
ETH2_3A+: J51.20 (P3A_P); also elsewhere on the board
ETH2_3A-: J51.18 (P3A_N); also elsewhere on the board
ETH2_3B+: J51.16 (P3B_P); also elsewhere on the board
ETH2_3B-: J51.14 (P3B_N); also elsewhere on the board
GND: J47.1 (GND1), J47.3 (GND2), J47.39 (GND3), J48.2, J51.1 (GND1), J51.3 (GND2), J51.39 (GND3), J52.2; also elsewhere on the board
unnamed: J47.40 (+3V3), J48.1
unnamed: J47.33 (P1A_N), J51.34 (P0A_N)
unnamed: J47.35 (P1A_P), J51.36 (P0A_P)
unnamed: J47.29 (P1B_N), J51.30 (P0B_N)
unnamed: J47.31 (P1B_P), J51.32 (P0B_P)
unnamed: J47.25 (P1C_N), J51.26 (P0C_N)
unnamed: J47.27 (P1C_P), J51.28 (P0C_P)
unnamed: J47.21 (P1D_N), J51.22 (P0D_N)
unnamed: J47.23 (P1D_P), J51.24 (P0D_P)
unnamed: J47.37 (SCK), J48.4
unnamed: J47.38 (SDA), J48.3
unnamed: J51.40 (+3V3), J52.1
unnamed: J51.37 (SCK), J52.4
unnamed: J51.38 (SDA), J52.3

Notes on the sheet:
PORT 6
PORT 3
For 1000Base-T operation, differential data from the media is transmitted and received on all four pairs. For 100Base-TX and 10Base-T operation, only MDIAP/N and MDIBP/N are used. Auto MDIX can reverse the pairs MDIAP/N and MDIBP/N. Each of the differential pairs has an internal 100-ohm termination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
PORT 4
PORT 2
PORT 1
PORT 5
